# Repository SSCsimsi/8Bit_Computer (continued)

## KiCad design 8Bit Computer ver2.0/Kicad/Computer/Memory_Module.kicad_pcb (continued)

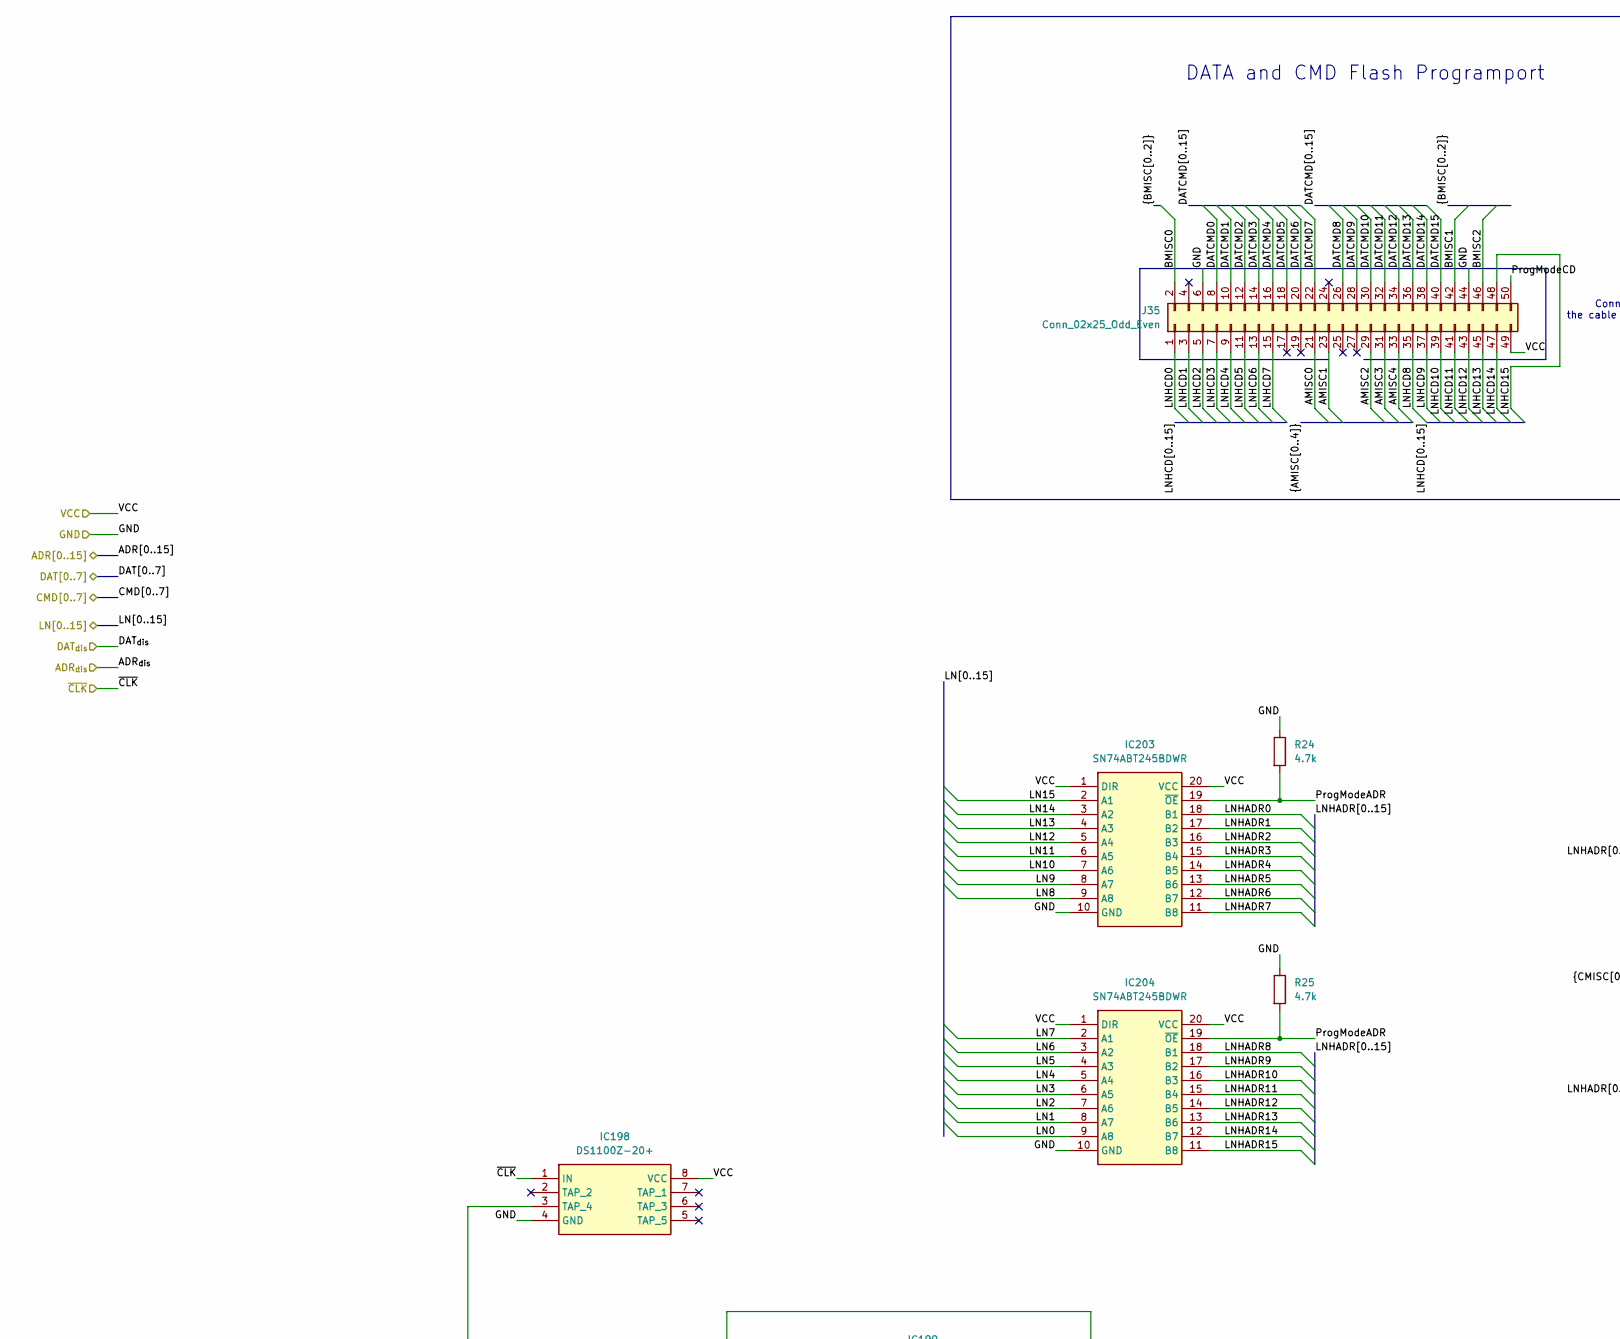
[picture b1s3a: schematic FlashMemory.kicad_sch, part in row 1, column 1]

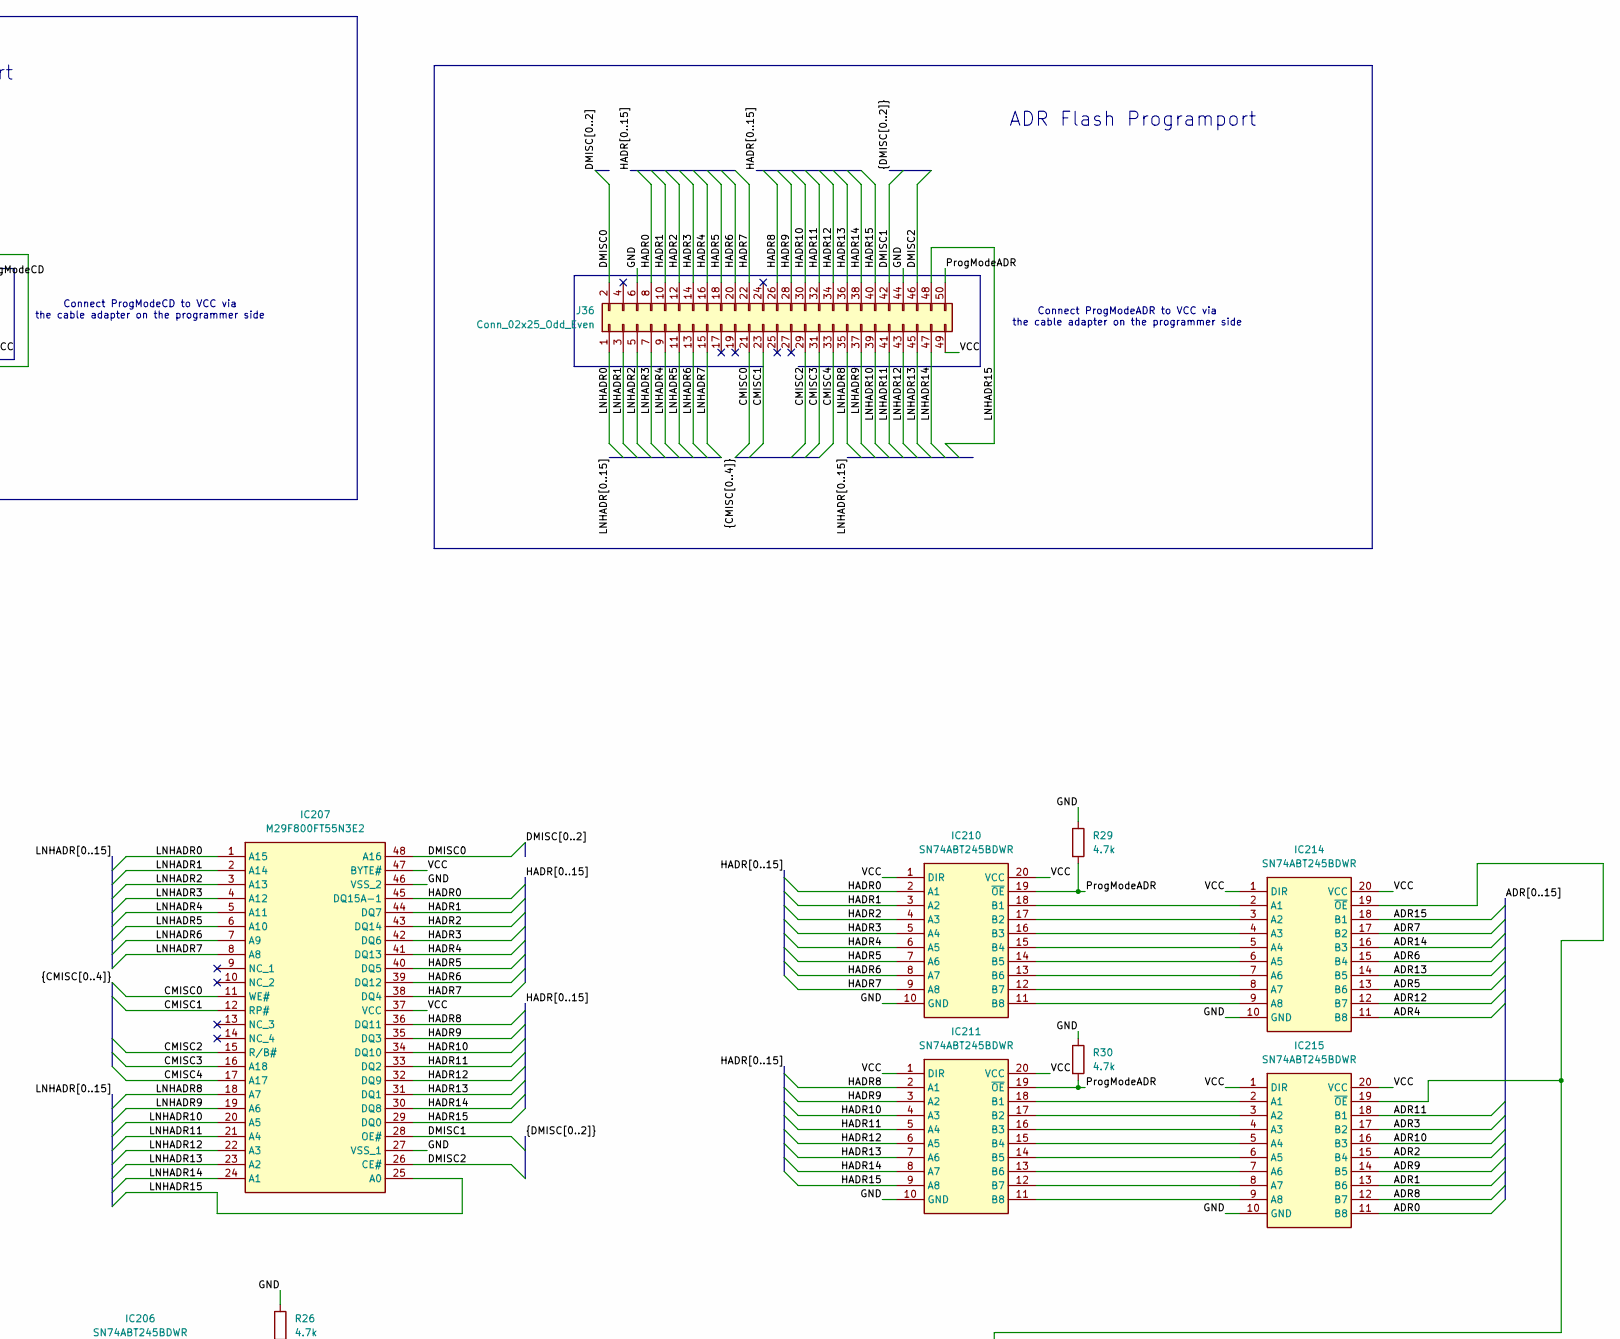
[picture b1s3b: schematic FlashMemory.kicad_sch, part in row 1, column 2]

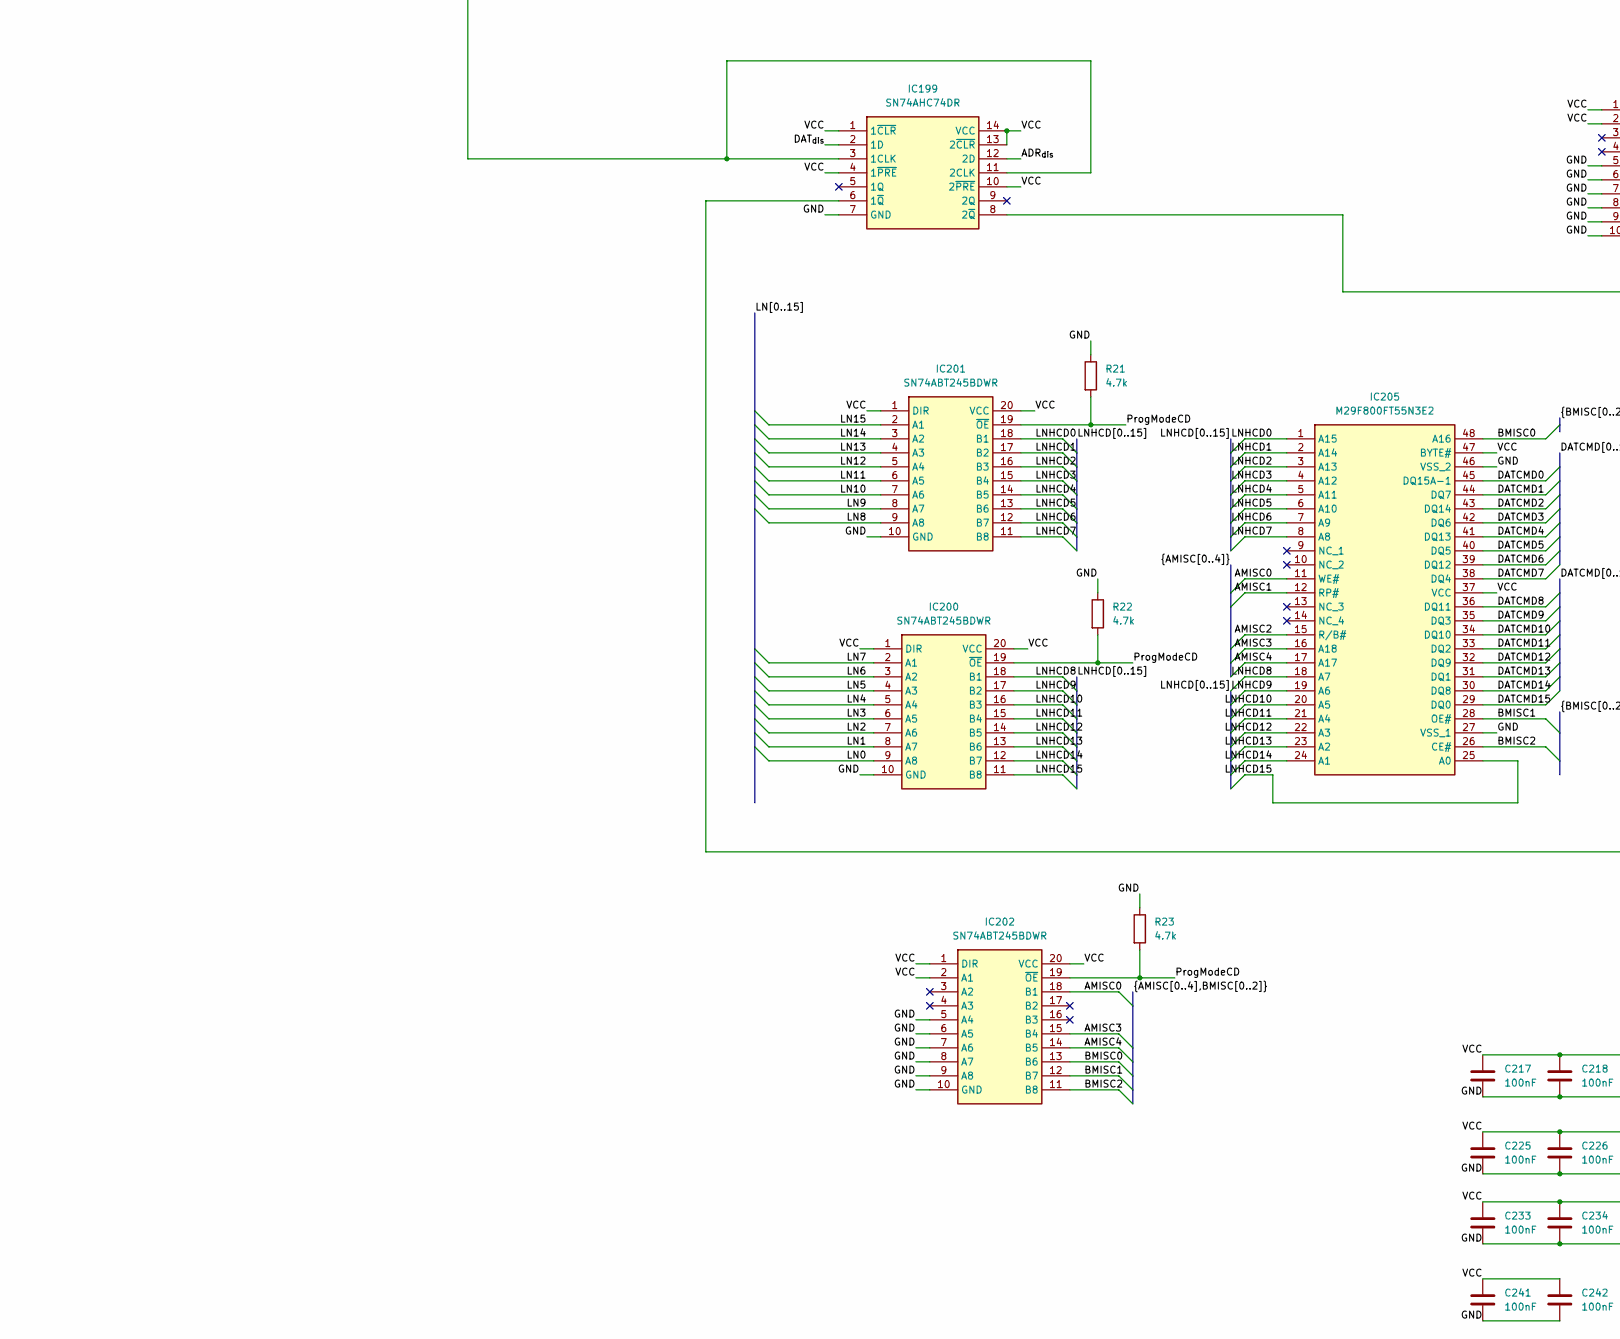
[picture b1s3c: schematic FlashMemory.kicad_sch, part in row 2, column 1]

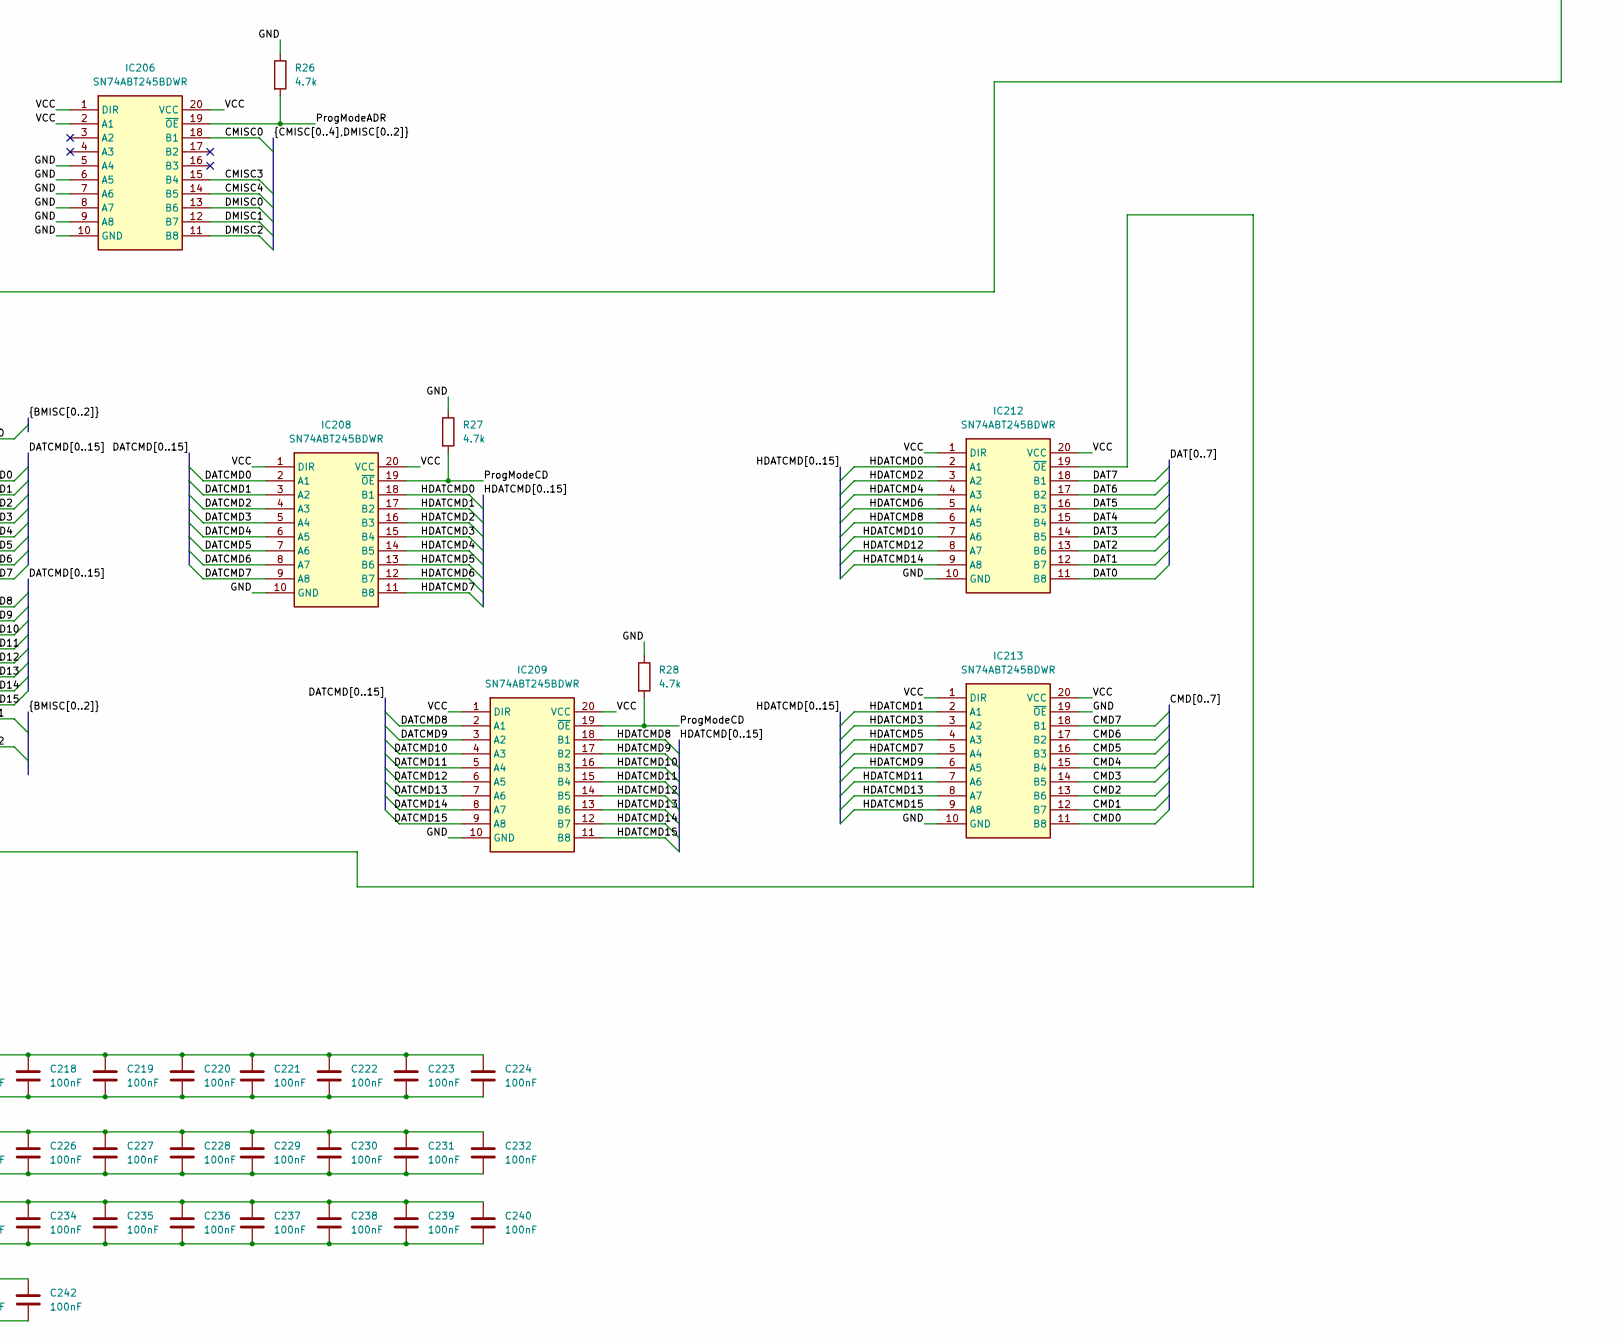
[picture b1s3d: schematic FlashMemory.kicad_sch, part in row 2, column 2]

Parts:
C217, C218, C219, C220, C221, C222, C223, C224, C225, C226, C227, C228, C229, C230, C231, C232, C233, C234, C235, C236, C237, C238, C239, C240, C241, C242: 100nF; C_1206_3216Metric_Pad1.33x1.80mm_HandSolder
IC198: DS1100Z-20+; SOIC127P600X175-8N; Mouser Part Number 700-DS1100Z-20
IC199: SN74AHC74DR; SOIC127P600X175-14N; Mouser Part Number 595-SN74AHC74DR
IC200, IC201, IC202, IC203, IC204, IC206, IC208, IC209, IC210, IC211, IC212, IC213, IC214, IC215: SN74ABT245BDWR; SOIC127P1030X265-20N; Mouser Part Number 595-SN74ABT245BDWR
IC205, IC207: M29F800FT55N3E2; SOP50P2000X120-48N; Mouser Part Number 913-M29F800FT55N3E2
J35, J36: Conn_02x25_Odd_Even; PinHeader_2x25_P2.54mm_Vertical
R21, R22, R23, R24, R25, R26, R27, R28, R29, R30: 4.7k; R_1206_3216Metric_Pad1.30x1.75mm_HandSolder

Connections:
/ADRM0: IC215.11 (B8); also elsewhere on the board
/ADRM1: IC215.13 (B6); also elsewhere on the board
/ADRM2: IC215.15 (B4); also elsewhere on the board
/ADRM3: IC215.17 (B2); also elsewhere on the board
/ADRM4: IC214.11 (B8); also elsewhere on the board
/ADRM5: IC214.13 (B6); also elsewhere on the board
/ADRM6: IC214.15 (B4); also elsewhere on the board
/ADRM7: IC214.17 (B2); also elsewhere on the board
/ADRM8: IC215.12 (B7); also elsewhere on the board
/ADRM9: IC215.14 (B5); also elsewhere on the board
/ADRM10: IC215.16 (B3); also elsewhere on the board
/ADRM11: IC215.18 (B1); also elsewhere on the board
/ADRM12: IC214.12 (B7); also elsewhere on the board
/ADRM13: IC214.14 (B5); also elsewhere on the board
/ADRM14: IC214.16 (B3); also elsewhere on the board
/ADRM15: IC214.18 (B1); also elsewhere on the board
/CMDM0: IC213.11 (B8); also elsewhere on the board
/CMDM1: IC213.12 (B7); also elsewhere on the board
/CMDM2: IC213.13 (B6); also elsewhere on the board
/CMDM3: IC213.14 (B5); also elsewhere on the board
/CMDM4: IC213.15 (B4); also elsewhere on the board
/CMDM5: IC213.16 (B3); also elsewhere on the board
/CMDM6: IC213.17 (B2); also elsewhere on the board
/CMDM7: IC213.18 (B1); also elsewhere on the board
/DATM0: IC212.11 (B8); also elsewhere on the board
/DATM1: IC212.12 (B7); also elsewhere on the board
/DATM2: IC212.13 (B6); also elsewhere on the board
/DATM3: IC212.14 (B5); also elsewhere on the board
/DATM4: IC212.15 (B4); also elsewhere on the board
/DATM5: IC212.16 (B3); also elsewhere on the board
/DATM6: IC212.17 (B2); also elsewhere on the board
/DATM7: IC212.18 (B1); also elsewhere on the board
/FlashMemory/ADR_{dis}: IC199.12 (2D); also elsewhere on the board
/FlashMemory/AMISC0: IC202.18 (B1), IC205.11 (WE#), J35.21
/FlashMemory/AMISC1: IC205.12 (RP#), J35.23
/FlashMemory/AMISC2: IC205.15 (R/B#), J35.29
/FlashMemory/AMISC3: IC202.15 (B4), IC205.16 (A18), J35.31
/FlashMemory/AMISC4: IC202.14 (B5), IC205.17 (A17), J35.33
/FlashMemory/BMISC0: IC202.13 (B6), IC205.48 (A16), J35.2
/FlashMemory/BMISC1: IC202.12 (B7), IC205.28 (OE#), J35.42
/FlashMemory/BMISC2: IC202.11 (B8), IC205.26 (CE#), J35.46
/FlashMemory/CMISC0: IC206.18 (B1), IC207.11 (WE#), J36.21
/FlashMemory/CMISC1: IC207.12 (RP#), J36.23
/FlashMemory/CMISC2: IC207.15 (R/B#), J36.29
/FlashMemory/CMISC3: IC206.15 (B4), IC207.16 (A18), J36.31
/FlashMemory/CMISC4: IC206.14 (B5), IC207.17 (A17), J36.33
/FlashMemory/DATCMD0: IC205.45 (DQ15A-1), IC208.2 (A1), J35.8
/FlashMemory/DATCMD1: IC205.44 (DQ7), IC208.3 (A2), J35.10
/FlashMemory/DATCMD2: IC205.43 (DQ14), IC208.4 (A3), J35.12
/FlashMemory/DATCMD3: IC205.42 (DQ6), IC208.5 (A4), J35.14
/FlashMemory/DATCMD4: IC205.41 (DQ13), IC208.6 (A5), J35.16
/FlashMemory/DATCMD5: IC205.40 (DQ5), IC208.7 (A6), J35.18
/FlashMemory/DATCMD6: IC205.39 (DQ12), IC208.8 (A7), J35.20
/FlashMemory/DATCMD7: IC205.38 (DQ4), IC208.9 (A8), J35.22
/FlashMemory/DATCMD8: IC205.36 (DQ11), IC209.2 (A1), J35.26
/FlashMemory/DATCMD9: IC205.35 (DQ3), IC209.3 (A2), J35.28
/FlashMemory/DATCMD10: IC205.34 (DQ10), IC209.4 (A3), J35.30
/FlashMemory/DATCMD11: IC205.33 (DQ2), IC209.5 (A4), J35.32
/FlashMemory/DATCMD12: IC205.32 (DQ9), IC209.6 (A5), J35.34
/FlashMemory/DATCMD13: IC205.31 (DQ1), IC209.7 (A6), J35.36
/FlashMemory/DATCMD14: IC205.30 (DQ8), IC209.8 (A7), J35.38
/FlashMemory/DATCMD15: IC205.29 (DQ0), IC209.9 (A8), J35.40
/FlashMemory/DAT_{dis}: IC199.2 (1D); also elsewhere on the board
/FlashMemory/DMISC0: IC206.13 (B6), IC207.48 (A16), J36.2
/FlashMemory/DMISC1: IC206.12 (B7), IC207.28 (OE#), J36.42
/FlashMemory/DMISC2: IC206.11 (B8), IC207.26 (CE#), J36.46
/FlashMemory/HADR0: IC207.45 (DQ15A-1), IC210.2 (A1), J36.8
/FlashMemory/HADR1: IC207.44 (DQ7), IC210.3 (A2), J36.10
/FlashMemory/HADR2: IC207.43 (DQ14), IC210.4 (A3), J36.12
/FlashMemory/HADR3: IC207.42 (DQ6), IC210.5 (A4), J36.14
/FlashMemory/HADR4: IC207.41 (DQ13), IC210.6 (A5), J36.16
/FlashMemory/HADR5: IC207.40 (DQ5), IC210.7 (A6), J36.18
/FlashMemory/HADR6: IC207.39 (DQ12), IC210.8 (A7), J36.20
/FlashMemory/HADR7: IC207.38 (DQ4), IC210.9 (A8), J36.22
/FlashMemory/HADR8: IC207.36 (DQ11), IC211.2 (A1), J36.26
/FlashMemory/HADR9: IC207.35 (DQ3), IC211.3 (A2), J36.28
/FlashMemory/HADR10: IC207.34 (DQ10), IC211.4 (A3), J36.30
/FlashMemory/HADR11: IC207.33 (DQ2), IC211.5 (A4), J36.32
/FlashMemory/HADR12: IC207.32 (DQ9), IC211.6 (A5), J36.34
/FlashMemory/HADR13: IC207.31 (DQ1), IC211.7 (A6), J36.36
/FlashMemory/HADR14: IC207.30 (DQ8), IC211.8 (A7), J36.38
/FlashMemory/HADR15: IC207.29 (DQ0), IC211.9 (A8), J36.40
/FlashMemory/HDATCMD0: IC208.18 (B1), IC212.2 (A1)
/FlashMemory/HDATCMD1: IC208.17 (B2), IC213.2 (A1)
/FlashMemory/HDATCMD2: IC208.16 (B3), IC212.3 (A2)
/FlashMemory/HDATCMD3: IC208.15 (B4), IC213.3 (A2)
/FlashMemory/HDATCMD4: IC208.14 (B5), IC212.4 (A3)
/FlashMemory/HDATCMD5: IC208.13 (B6), IC213.4 (A3)
/FlashMemory/HDATCMD6: IC208.12 (B7), IC212.5 (A4)
/FlashMemory/HDATCMD7: IC208.11 (B8), IC213.5 (A4)
/FlashMemory/HDATCMD8: IC209.18 (B1), IC212.6 (A5)
/FlashMemory/HDATCMD9: IC209.17 (B2), IC213.6 (A5)
/FlashMemory/HDATCMD10: IC209.16 (B3), IC212.7 (A6)
/FlashMemory/HDATCMD11: IC209.15 (B4), IC213.7 (A6)
/FlashMemory/HDATCMD12: IC209.14 (B5), IC212.8 (A7)
/FlashMemory/HDATCMD13: IC209.13 (B6), IC213.8 (A7)
/FlashMemory/HDATCMD14: IC209.12 (B7), IC212.9 (A8)
/FlashMemory/HDATCMD15: IC209.11 (B8), IC213.9 (A8)
/FlashMemory/LNHADR0: IC203.18 (B1), IC207.1 (A15), J36.1
/FlashMemory/LNHADR1: IC203.17 (B2), IC207.2 (A14), J36.3
/FlashMemory/LNHADR2: IC203.16 (B3), IC207.3 (A13), J36.5
/FlashMemory/LNHADR3: IC203.15 (B4), IC207.4 (A12), J36.7
/FlashMemory/LNHADR4: IC203.14 (B5), IC207.5 (A11), J36.9
/FlashMemory/LNHADR5: IC203.13 (B6), IC207.6 (A10), J36.11
/FlashMemory/LNHADR6: IC203.12 (B7), IC207.7 (A9), J36.13
/FlashMemory/LNHADR7: IC203.11 (B8), IC207.8 (A8), J36.15
/FlashMemory/LNHADR8: IC204.18 (B1), IC207.18 (A7), J36.35
/FlashMemory/LNHADR9: IC204.17 (B2), IC207.19 (A6), J36.37
/FlashMemory/LNHADR10: IC204.16 (B3), IC207.20 (A5), J36.39
/FlashMemory/LNHADR11: IC204.15 (B4), IC207.21 (A4), J36.41
/FlashMemory/LNHADR12: IC204.14 (B5), IC207.22 (A3), J36.43
/FlashMemory/LNHADR13: IC204.13 (B6), IC207.23 (A2), J36.45
/FlashMemory/LNHADR14: IC204.12 (B7), IC207.24 (A1), J36.47
/FlashMemory/LNHADR15: IC204.11 (B8), IC207.25 (A0), J36.48
/FlashMemory/LNHCD0: IC201.18 (B1), IC205.1 (A15), J35.1
/FlashMemory/LNHCD1: IC201.17 (B2), IC205.2 (A14), J35.3
/FlashMemory/LNHCD2: IC201.16 (B3), IC205.3 (A13), J35.5
/FlashMemory/LNHCD3: IC201.15 (B4), IC205.4 (A12), J35.7
/FlashMemory/LNHCD4: IC201.14 (B5), IC205.5 (A11), J35.9
/FlashMemory/LNHCD5: IC201.13 (B6), IC205.6 (A10), J35.11
/FlashMemory/LNHCD6: IC201.12 (B7), IC205.7 (A9), J35.13
/FlashMemory/LNHCD7: IC201.11 (B8), IC205.8 (A8), J35.15
/FlashMemory/LNHCD8: IC200.18 (B1), IC205.18 (A7), J35.35
/FlashMemory/LNHCD9: IC200.17 (B2), IC205.19 (A6), J35.37
/FlashMemory/LNHCD10: IC200.16 (B3), IC205.20 (A5), J35.39
/FlashMemory/LNHCD11: IC200.15 (B4), IC205.21 (A4), J35.41
/FlashMemory/LNHCD12: IC200.14 (B5), IC205.22 (A3), J35.43
/FlashMemory/LNHCD13: IC200.13 (B6), IC205.23 (A2), J35.45
/FlashMemory/LNHCD14: IC200.12 (B7), IC205.24 (A1), J35.47
/FlashMemory/LNHCD15: IC200.11 (B8), IC205.25 (A0), J35.48
/FlashMemory/ProgModeADR: IC203.19 (~OE), IC204.19 (~OE), IC206.19 (~OE), IC210.19 (~OE), IC211.19 (~OE), J36.50, R24.2, R25.2, R26.2, R29.2, R30.2
/FlashMemory/ProgModeCD: IC200.19 (~OE), IC201.19 (~OE), IC202.19 (~OE), IC208.19 (~OE), IC209.19 (~OE), J35.50, R21.2, R22.2, R23.2, R27.2, R28.2
/FlashMemory/~CLK: IC198.1 (IN); also elsewhere on the board
/GNDM: C217.1, C218.1, C219.1, C220.1, C221.1, C222.1, C223.1, C224.1, C225.1, C226.1, C227.1, C228.1, C229.1, C230.1, C231.1, C232.1, C233.1, C234.1, C235.1, C236.1, C237.1, C238.1, C239.1, C240.1, C241.1, C242.1, IC198.4 (GND), IC199.7 (GND), IC200.10 (GND), IC201.10 (GND), IC202.5 (A4), IC202.6 (A5), IC202.7 (A6), IC202.8 (A7), IC202.9 (A8), IC202.10 (GND), IC203.10 (GND), IC204.10 (GND), IC205.27 (VSS_1), IC205.46 (VSS_2), IC206.5 (A4), IC206.6 (A5), IC206.7 (A6), IC206.8 (A7), IC206.9 (A8), IC206.10 (GND), IC207.27 (VSS_1), IC207.46 (VSS_2), IC208.10 (GND), IC209.10 (GND), IC210.10 (GND), IC211.10 (GND), IC212.10 (GND), IC213.10 (GND), IC213.19 (~OE), IC214.10 (GND), IC215.10 (GND), J35.6, J35.44, J36.6, J36.44, R21.1, R22.1, R23.1, R24.1, R25.1, R26.1, R27.1, R28.1, R29.1, R30.1; also elsewhere on the board
/LNM0: IC200.9 (A8), IC204.9 (A8); also elsewhere on the board
/LNM1: IC200.8 (A7), IC204.8 (A7); also elsewhere on the board
/LNM2: IC200.7 (A6), IC204.7 (A6); also elsewhere on the board
/LNM3: IC200.6 (A5), IC204.6 (A5); also elsewhere on the board
/LNM4: IC200.5 (A4), IC204.5 (A4); also elsewhere on the board
/LNM5: IC200.4 (A3), IC204.4 (A3); also elsewhere on the board
/LNM6: IC200.3 (A2), IC204.3 (A2); also elsewhere on the board
/LNM7: IC200.2 (A1), IC204.2 (A1); also elsewhere on the board
/LNM8: IC201.9 (A8), IC203.9 (A8); also elsewhere on the board
/LNM9: IC201.8 (A7), IC203.8 (A7); also elsewhere on the board
/LNM10: IC201.7 (A6), IC203.7 (A6); also elsewhere on the board
/LNM11: IC201.6 (A5), IC203.6 (A5); also elsewhere on the board
/LNM12: IC201.5 (A4), IC203.5 (A4); also elsewhere on the board
/LNM13: IC201.4 (A3), IC203.4 (A3); also elsewhere on the board
/LNM14: IC201.3 (A2), IC203.3 (A2); also elsewhere on the board
/LNM15: IC201.2 (A1), IC203.2 (A1); also elsewhere on the board
/VCCM: C217.2, C218.2, C219.2, C220.2, C221.2, C222.2, C223.2, C224.2, C225.2, C226.2, C227.2, C228.2, C229.2, C230.2, C231.2, C232.2, C233.2, C234.2, C235.2, C236.2, C237.2, C238.2, C239.2, C240.2, C241.2, C242.2, IC198.8 (VCC), IC199.1 (1~CLR), IC199.4 (1~PRE), IC199.10 (2~PRE), IC199.13 (2~CLR), IC199.14 (VCC), IC200.1 (DIR), IC200.20 (VCC), IC201.1 (DIR), IC201.20 (VCC), IC202.1 (DIR), IC202.2 (A1), IC202.20 (VCC), IC203.1 (DIR), IC203.20 (VCC), IC204.1 (DIR), IC204.20 (VCC), IC205.37 (VCC), IC205.47 (BYTE#), IC206.1 (DIR), IC206.2 (A1), IC206.20 (VCC), IC207.37 (VCC), IC207.47 (BYTE#), IC208.1 (DIR), IC208.20 (VCC), IC209.1 (DIR), IC209.20 (VCC), IC210.1 (DIR), IC210.20 (VCC), IC211.1 (DIR), IC211.20 (VCC), IC212.1 (DIR), IC212.20 (VCC), IC213.1 (DIR), IC213.20 (VCC), IC214.1 (DIR), IC214.20 (VCC), IC215.1 (DIR), IC215.20 (VCC), J35.49, J36.49; also elsewhere on the board
unnamed: IC198.3 (TAP_4), IC199.3 (1CLK), IC199.11 (2CLK)
unnamed: IC199.6 (1~Q), IC212.19 (~OE)
unnamed: IC199.8 (2~Q), IC214.19 (~OE), IC215.19 (~OE)
unnamed: IC210.18 (B1), IC214.2 (A1)
unnamed: IC210.17 (B2), IC214.3 (A2)
unnamed: IC210.16 (B3), IC214.4 (A3)
unnamed: IC210.15 (B4), IC214.5 (A4)
unnamed: IC210.14 (B5), IC214.6 (A5)
unnamed: IC210.13 (B6), IC214.7 (A6)
unnamed: IC210.12 (B7), IC214.8 (A7)
unnamed: IC210.11 (B8), IC214.9 (A8)
unnamed: IC211.18 (B1), IC215.2 (A1)
unnamed: IC211.17 (B2), IC215.3 (A2)
unnamed: IC211.16 (B3), IC215.4 (A3)
unnamed: IC211.15 (B4), IC215.5 (A4)
unnamed: IC211.14 (B5), IC215.6 (A5)
unnamed: IC211.13 (B6), IC215.7 (A6)
unnamed: IC211.12 (B7), IC215.8 (A7)
unnamed: IC211.11 (B8), IC215.9 (A8)

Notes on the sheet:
Connect ProgModeCD to VCC via the cable adapter on the programmer side
ADR Flash Programport
DATA and CMD Flash Programport
Connect ProgModeADR to VCC via the cable adapter on the programmer side

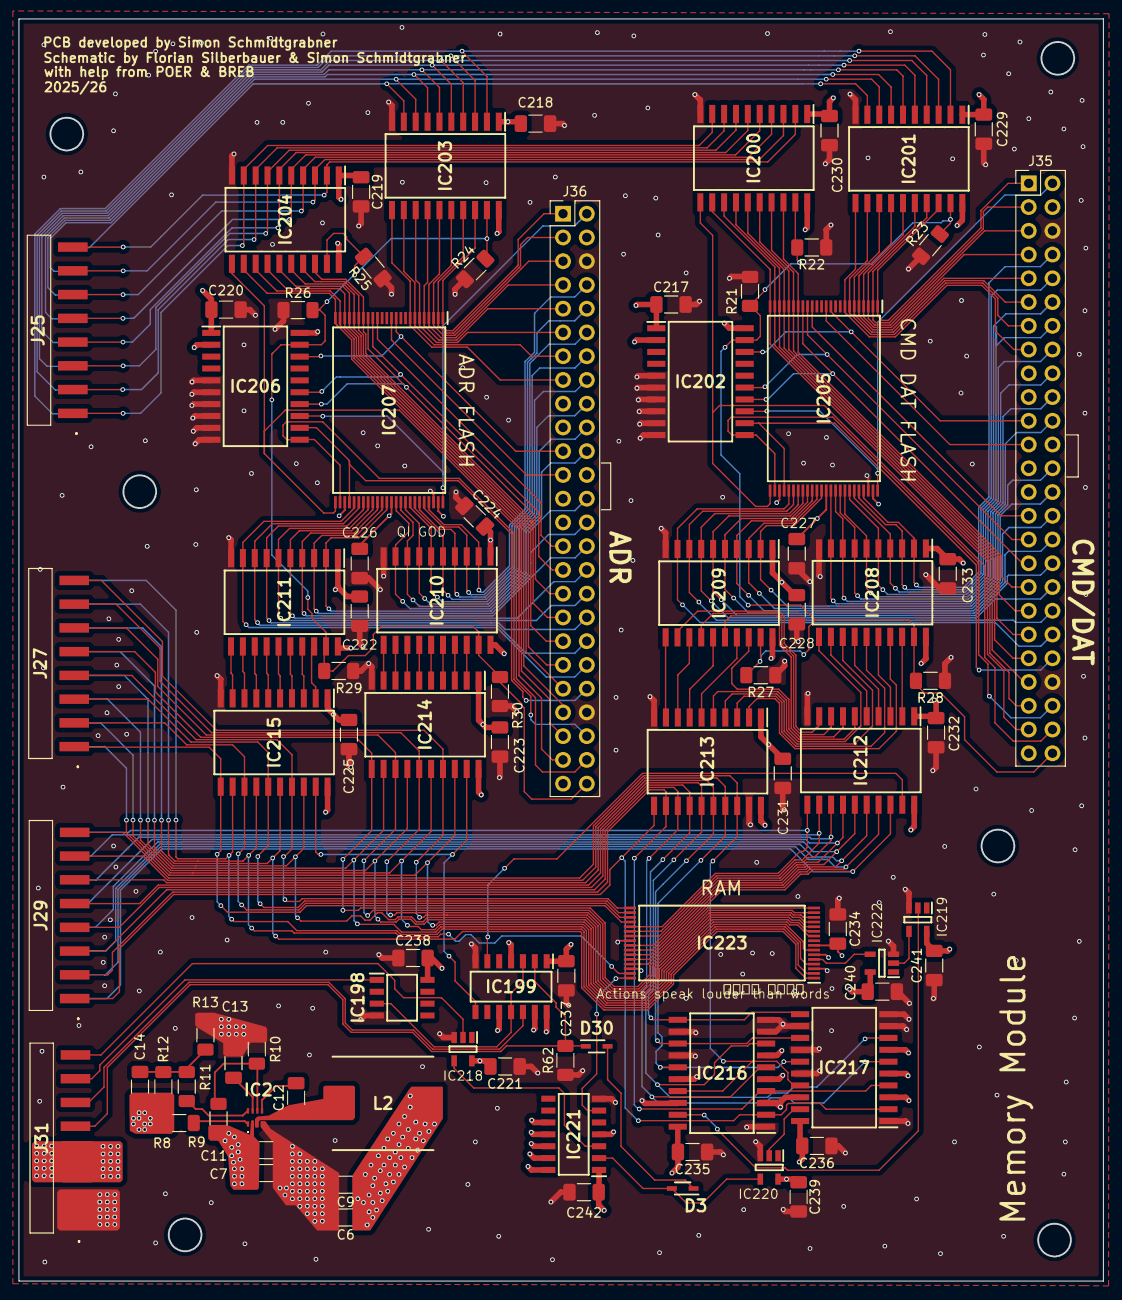
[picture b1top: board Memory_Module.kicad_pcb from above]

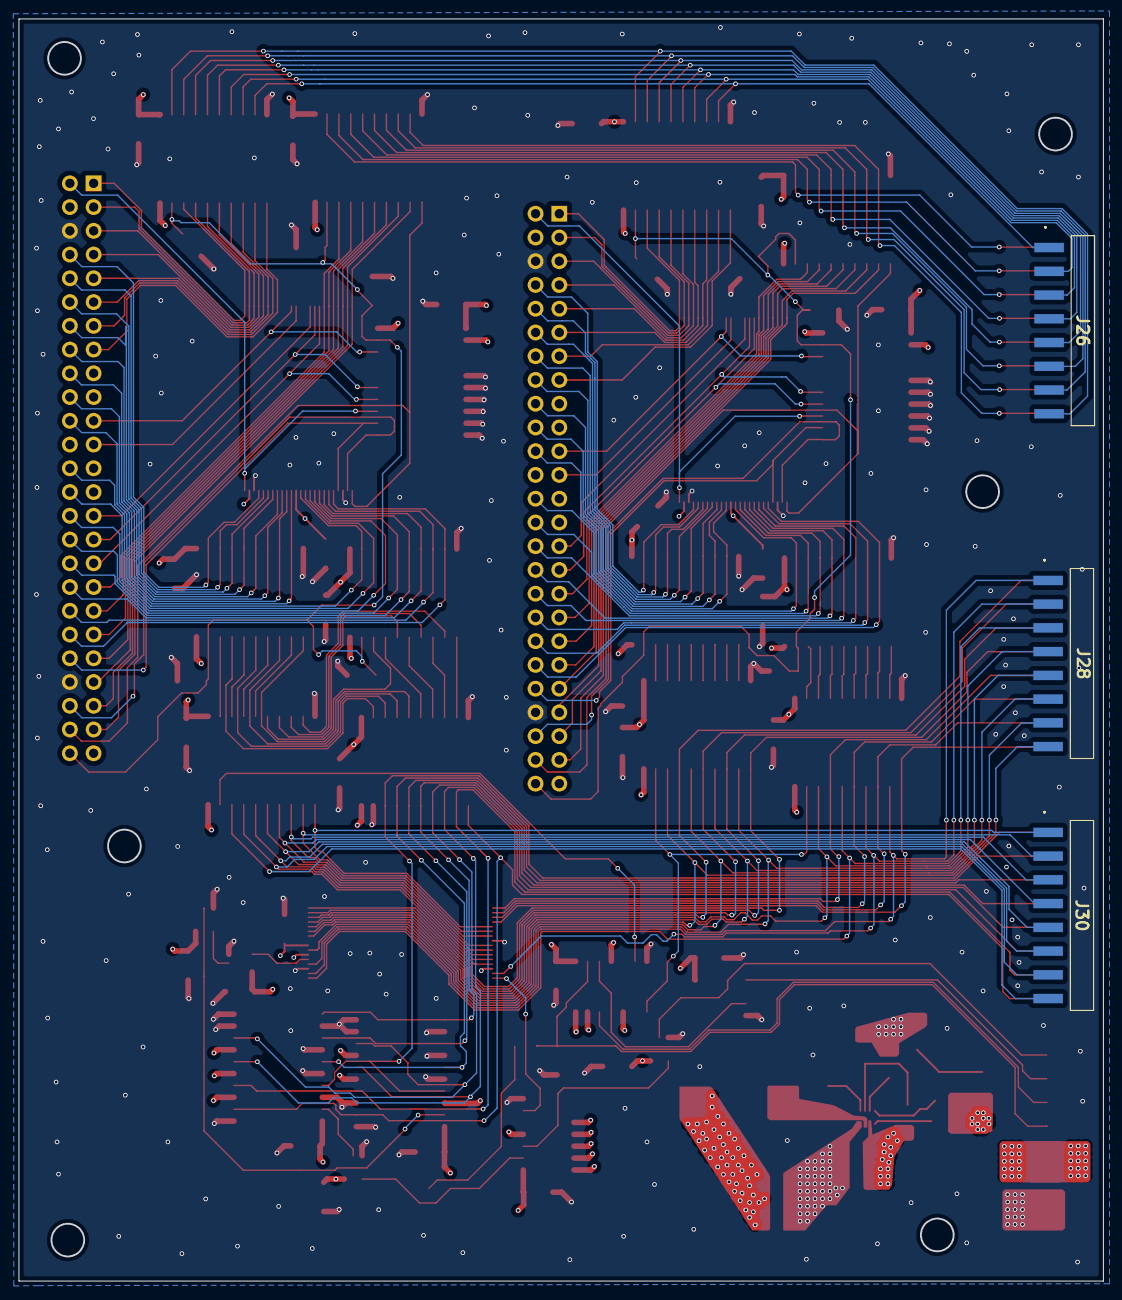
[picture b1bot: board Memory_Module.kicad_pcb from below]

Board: 4 copper layers, 116.0 x 135.0 mm, 89 parts (3 on the bottom side), 187 nets.

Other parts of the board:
D30: 1N4148WS-7-F; SOD2513X120N

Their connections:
/FlashMemory/DAT_{dis}: D30.1 (K); also elsewhere on the board
/RAM/DAT_{dis}: D30.2 (A); also elsewhere on the board
